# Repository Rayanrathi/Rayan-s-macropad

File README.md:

# Rayan's Macropad

A custom 4-key macropad with a rotary encoder and OLED display, built as part of Hack Club's PCB design program.

---

## Renders & Screenshots

### PCB 3D Render

### Schematic

### PCB Layout

### Case — Bottom

### Case — Lid

---

## Features

- 4x tactile push switches (SW1–SW4)
- EC11 rotary encoder with push button (SW6)
- 0.91" 128×32 OLED display
- Seeeduino XIAO SAMD21 microcontroller
- QMK firmware with layer support and WPM counter
- Custom 3D printed sandwich-mount case

---

## Bill of Materials

| Part | Quantity | Notes |
|------|----------|-------|
| Seeeduino XIAO SAMD21 | 1 | Main MCU |
| Tactile push switch | 4 | SW1–SW4 |
| EC11 Rotary Encoder | 1 | SW6, with push button |
| 0.91" SSD1306 OLED (128×32) | 1 | I2C, 4-pin, J1 connector |
| M2.9 screws | 4 | Sandwich mount lid to base |
| Custom PCB | 1 | 97mm × 49.5mm, see /PCB |
| 3D printed case (top + bottom) | 1 set | See /CAD |

---

## Pin Assignments

| Component | XIAO Pin |
|-----------|----------|
| SW1 | A0 (PA02) |
| SW2 | A1 (PA4) |
| SW3 | A2 (PA10) |
| SW4 | A3 (PA11) |
| OLED SDA | A4 (PA8) |
| OLED SCL | A5 (PA9) |
| Encoder A | A8 (PA5) |
| Encoder B | A9 (PA7) |

All switches are wired directly (no matrix) — one side to GND, other side to pin.

---

## PCB

Designed in KiCad. Board size: 97mm × 49.5mm.
To order, use `production/gerbers.zip` with JLCPCB or PCBWay.

---

## Case

Designed in OpenSCAD. Sandwich-mount style.
- Base: 3mm floor + 10mm walls = 13mm total height
- Lid: 3mm thick with switch holes, OLED window, encoder shaft hole

Export STLs from `case_bottom.scad` and `case_lid.scad` → F6 → Export as STL.

---

## Firmware

Built with QMK. See `/Firmware/` folder.

**Default keymap:**

| Key | Base | FN |
|-----|------|----|
| SW1 | 1 | F1 |
| SW2 | 2 | F2 |
| SW3 | 3 | F3 |
| SW4 | 4 | F4 |
| Knob CW | Vol Up | Next Track |
| Knob CCW | Vol Down | Prev Track |

OLED shows: keyboard name, current layer, encoder hint, WPM counter.

**To flash:**
```bash
qmk compile -kb rayan_macropad -km default
```
Double-tap RST on XIAO → open QMK Toolbox → load `.bin` → Flash.

---

## Build Guide

1. Solder XIAO onto PCB
2. Solder SW1–SW4 switches
3. Solder EC11 rotary encoder (SW6)
4. Connect OLED to J1 connector
5. 3D print top and bottom case
6. Place PCB into bottom case
7. Screw lid on with 4x M2.9 screws
8. Flash QMK firmware

---

## File Structure

```
your-macropad/
├── README.md
├── images/
│   ├── pcb_3d.jpg
│   ├── schematic.jpg
│   ├── pcb_layout.jpg
│   ├── case_bottom.jpg
│   └── case_lid.jpg
├── CAD/
│   └── assembled-model.STEP
├── PCB/
│   ├── your-project.kicad_pro
│   ├── your-project.kicad_sch
│   └── your-project.kicad_pcb
├── Firmware/
│   └── rayan_macropad/
└── production/
    ├── gerbers.zip
    ├── Top.STEP
    ├── Bottom.STEP
    └── firmware.uf2
```

---

*Made with ❤️ as part of [Hack Club](https://hackclub.com)*

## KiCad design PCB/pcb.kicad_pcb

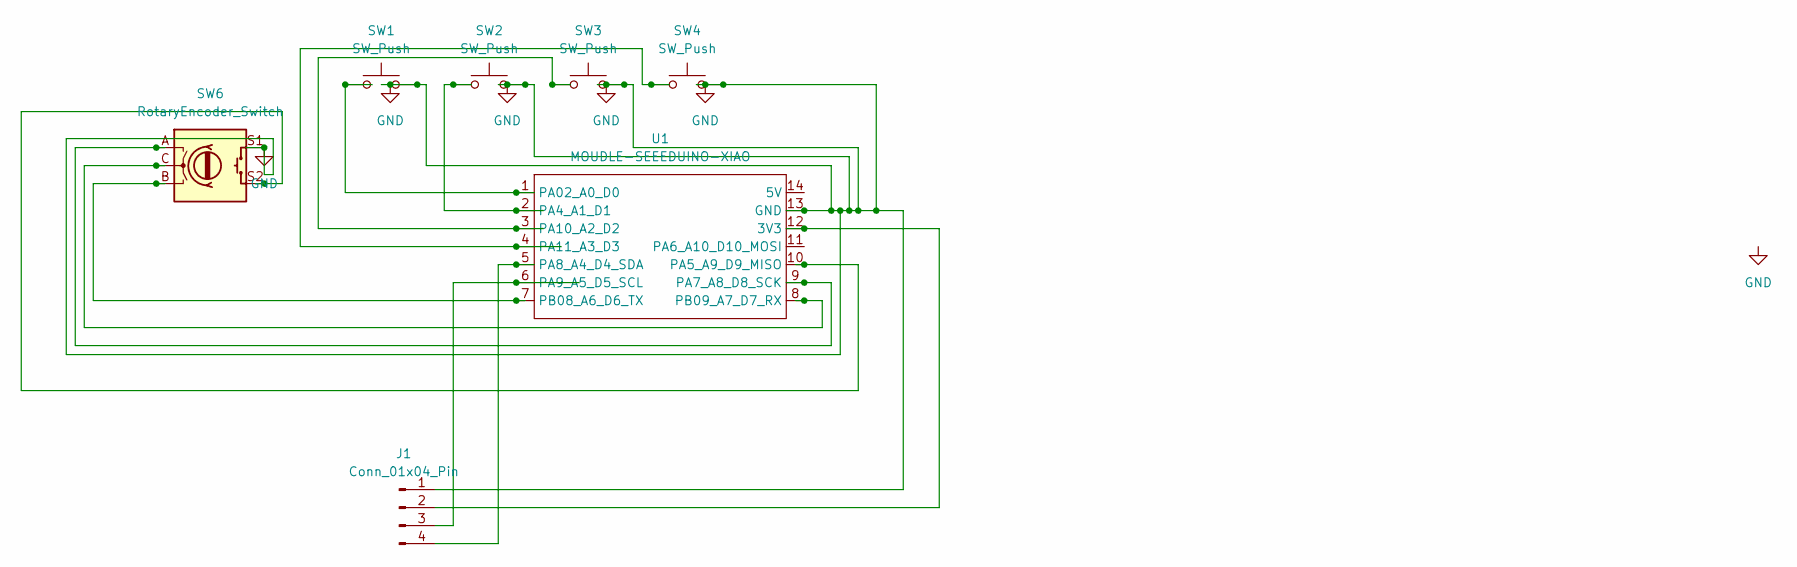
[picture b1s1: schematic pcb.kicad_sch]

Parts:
J1: Conn_01x04_Pin; PinHeader_1x04_P2.54mm_Vertical
SW1, SW2, SW3, SW4: SW_Push; SW_Cherry_MX_1.00u_PCB
SW6: RotaryEncoder_Switch; RotaryEncoder_Alps_EC11E-Switch_Vertical_H20mm
U1: MOUDLE-SEEEDUINO-XIAO; XIAO-Generic-Hybrid-14P-2.54-21X17.8MM

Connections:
GND: J1.1, SW1.2, SW2.2, SW3.2, SW4.2, SW6.S1, U1.13 (GND)
unnamed: J1.2, U1.12 (3V3)
unnamed: J1.3, U1.6 (PA9_A5_D5_SCL)
unnamed: J1.4, U1.5 (PA8_A4_D4_SDA)
unnamed: SW1.1, U1.1 (PA02_A0_D0)
unnamed: SW2.1, U1.2 (PA4_A1_D1)
unnamed: SW6.S2, U1.10 (PA5_A9_D9_MISO)
unnamed: SW6.A, U1.9 (PA7_A8_D8_SCK)
unnamed: SW3.1, U1.3 (PA10_A2_D2)
unnamed: SW4.1, U1.4 (PA11_A3_D3)
unnamed: SW6.B, U1.7 (PB08_A6_D6_TX)
unnamed: SW6.C, U1.8 (PB09_A7_D7_RX)

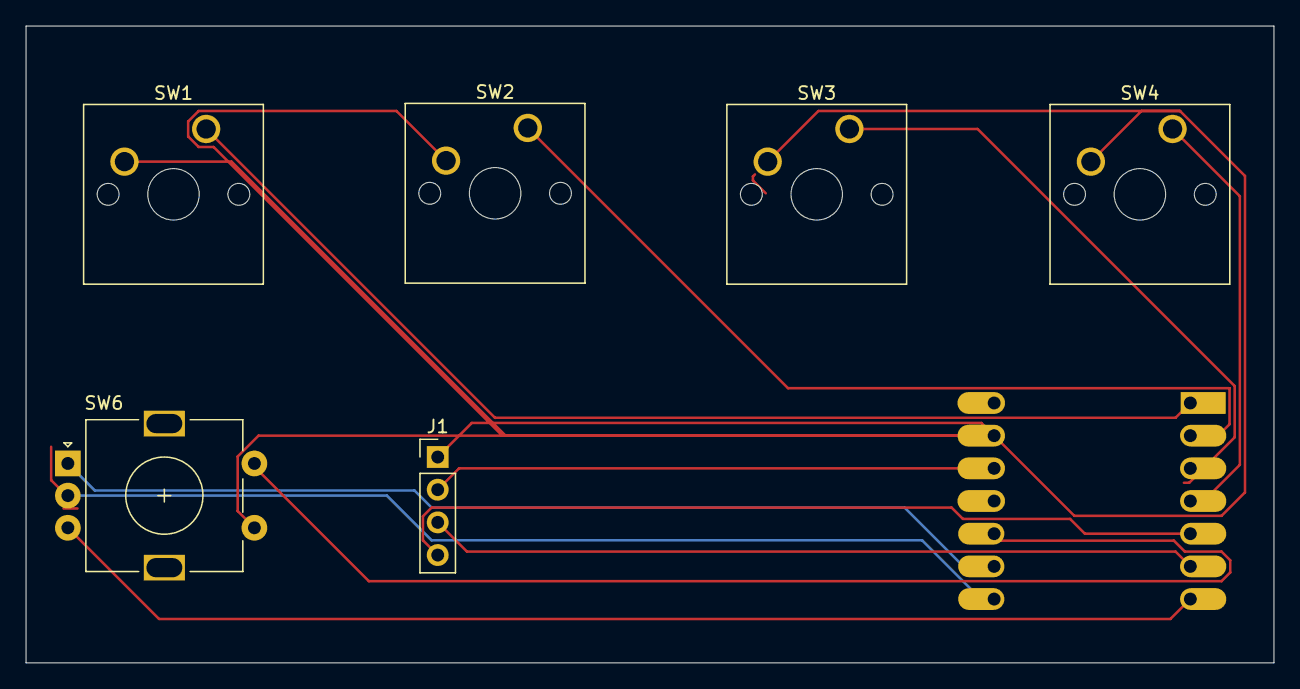
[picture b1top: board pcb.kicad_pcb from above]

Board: 2 copper layers, 97.0 x 49.5 mm, 7 parts (1 on the bottom side), 12 nets.
